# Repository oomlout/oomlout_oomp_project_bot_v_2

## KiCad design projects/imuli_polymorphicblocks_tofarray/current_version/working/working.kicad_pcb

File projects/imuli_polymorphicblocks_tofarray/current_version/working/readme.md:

# polymorphicblocks
 
## summary 
* id: imuli_polymorphicblocks_tofarray
* user: imuli
* name: polymorphicblocks
* board: tofarray
* repo: https://github.com/imuli/PolymorphicBlocks
* src_file_repo_kicad_pcb: examples/TofArray/TofArray.kicad_pcb
* src_file_repo_kicad_pcb_link: https://github.com/imuli/PolymorphicBlocks/tree/master/examples/TofArray/TofArray.kicad_pcb

* src_file_repo_sch: 
* src_file_repo_sch_link: https://github.com/imuli/PolymorphicBlocks/tree/master/
* full details link: https://github.com/oomlout/oomlout_oomp_project_bot_v_2/tree/main/projects/imuli_polymorphicblocks_tofarray/current_version/working

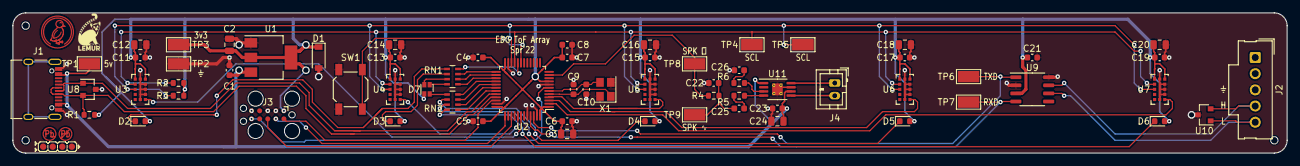
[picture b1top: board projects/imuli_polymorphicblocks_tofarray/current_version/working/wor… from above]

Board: 2 copper layers, 200.0 x 22.0 mm, 74 parts (0 on the bottom side), 47 nets.

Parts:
1: Indicator_LeadFree
2: Indicator_IdDots_4
C1, C4, C5, C6, C11, C13, C15, C17, C19, C21, C23: C14663; C_0603_1608Metric
C2, C3, C12, C14, C16, C18, C20, C24: C1779; C_0805_2012Metric
C7: C57112; C_0603_1608Metric
C8, C25, C26: C15849; C_0603_1608Metric
C9, C10: C1663; C_0603_1608Metric
C22: C1622; C_0603_1608Metric
D1: C499796; D_SOD-123
D2, D3, D4, D5, D6: C2286; LED_0603_1608Metric
D7: C264517; LED_LiteOn_LTST-C19HE1WT
H1, H2, H3: JlcToolingHole_1.152mm
J1: C165948; USB_C_Receptacle_XKB_U262-16XN-4BVC11
J2: Molex_SL_171971-0005_1x05_P2.54mm_Vertical
J3: Tag-Connect_TC2050-IDC-FP_2x05_P1.27mm_Vertical
J4: JST_PH_B2B-PH-K_1x02_P2.00mm_Vertical
R1: C22843; R_0603_1608Metric
R2, R3: C23162; R_0603_1608Metric
R4: C21190; R_0603_1608Metric
R5, R6: C22984; R_0603_1608Metric
RN1, RN2: C20197; R_Array_Concave_4x0603
SW1: C318884; SW_SPST_SKQG_WithoutStem
TP1, TP2, TP3, TP4, TP5, TP6, TP7, TP8, TP9: C238130; TestPoint_Keystone_5015_Micro-Minature
U1: C86781; SOT-223-3_TabPin2
U2: C8734; LQFP-48_7x7mm_P0.5mm
U3, U4, U5, U6, U7: C91199; ST_VL53L0X
U8: C87911; SOT-23
U9: C12084; SO-8_3.9x4.9mm_P1.27mm
U10: SOT-23
U11: C27396; MSOP-8-1EP_3x3mm_P0.65mm_EP1.68x1.88mm_ThermalVias
U12: Symbol_Duckling
U13: Symbol_LemurSmall
X1: C9002; Crystal_SMD_3225-4Pin_3.2x2.5mm

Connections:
can_chain_0.rxd: TP7.1, U2.45, U9.4
can_chain_0.txd: TP6.1, U2.46, U9.1
can_chain_1.canh: J2.4, U9.7, U10.2
can_chain_1.canl: J2.5, U9.6, U10.1
gnd: C1.2, C2.2, C3.2, C4.2, C5.2, C6.2, C7.2, C8.2, C9.2, C10.2, C11.2, C12.2, C13.2, C14.2, C15.2, C16.2, C17.2, C18.2, C19.2, C20.2, C21.2, C22.2, C23.2, C24.2, C26.2, D1.2, J1.A1, J1.A12, J1.B1, J1.B12, J2.3, J3.2, J3.3, J3.5, SW1.1, TP2.1, U1.1, U2.8, U2.23, U2.35, U2.44, U2.47, U3.2, U3.3, U3.4, U3.6, U3.12, U4.2, U4.3, U4.4, U4.6, U4.12, U5.2, U5.3, U5.4, U5.6, U5.12, U6.2, U6.3, U6.4, U6.6, U6.12, U7.2, U7.3, U7.4, U7.6, U7.12, U8.3, U9.2, U9.8, U10.3, U11.7, U11.9, X1.2, X1.4
i2c_chain_0.scl: R2.2, TP4.1, U2.21, U3.10, U4.10, U5.10, U6.10, U7.10
i2c_chain_0.sda: R3.2, TP5.1, U2.22, U3.9, U4.9, U5.9, U6.9, U7.9
leds_chain_0.0: RN1.8, U2.20
leds_chain_0.1: RN1.7, U2.25
leds_chain_0.2: RN2.7, U2.29
leds_chain_0.3: RN2.6, U2.30
leds_chain_0.4: RN2.5, U2.31
leds_chain_0.5: RN1.6, U2.26
leds_chain_0.6: RN1.5, U2.27
leds_chain_0.7: RN2.8, U2.28
mcu.crystal.crystal.a: C9.1, U2.5, X1.1
mcu.gpio.tof_xshut_1: U2.41, U4.5
mcu.gpio.tof_xshut_2: U2.4, U5.5
mcu.gpio.tof_xshut_3: U2.3, U6.5
mcu.ic.osc.xtal_out: C10.1, U2.6, X1.3
mcu.ic.swd.swclk: J3.9, U2.37
mcu.ic.swd.swo: J3.8, U2.39
mcu.swd.swd.reset: J3.6, U2.7
mcu.swd.swd.swdio: J3.10, U2.34
res1.a.0: D2.1, RN1.1
res1.a.1: D3.1, RN1.2
res1.a.2: D7.3, RN1.3
res1.a.3: D7.4, RN1.4
res2.a.0: D7.1, RN2.1
res2.a.1: D4.1, RN2.2
res2.a.2: D5.1, RN2.3
res2.a.3: D6.1, RN2.4
spk_chain_0: R4.1, TP8.1, U2.11
spk_chain_1: C22.1, C25.2, R4.2, TP9.1
spk_chain_2.a: J4.1, U11.8
spk_chain_2.b: J4.2, U11.5
spk_drv.(adapter)inn_res.b.src: R6.2, U11.3
spk_drv.(adapter)inp_res.b.dst: R5.2, U11.4
spk_drv.inn_cap.pos: C26.1, R6.1
spk_drv.inp_res.a: C25.1, R5.1
sw1_chain_0: SW1.2, U2.19
tof.xshut.0: U2.42, U3.5
tof.xshut.4: U2.2, U7.5
usb_chain_0.d_N: J1.A7, J1.B7, U2.32, U8.1
usb_chain_0.d_P: J1.A6, J1.B6, R1.2, U2.33, U8.2
v3v3: C2.1, C3.1, C4.1, C5.1, C6.1, C7.1, C8.1, C11.1, C12.1, C13.1, C14.1, C15.1, C16.1, C17.1, C18.1, C19.1, C20.1, C21.1, D1.1, D2.2, D3.2, D4.2, D5.2, D6.2, D7.2, J3.1, R1.1, R2.1, R3.1, TP3.1, U1.2, U2.1, U2.9, U2.24, U2.36, U2.48, U3.1, U3.11, U4.1, U4.11, U5.1, U5.11, U6.1, U6.11, U7.1, U7.11, U9.3
vusb: C1.1, C23.1, C24.1, J1.A4, J1.A9, J1.B4, J1.B9, TP1.1, U1.3, U11.1, U11.6

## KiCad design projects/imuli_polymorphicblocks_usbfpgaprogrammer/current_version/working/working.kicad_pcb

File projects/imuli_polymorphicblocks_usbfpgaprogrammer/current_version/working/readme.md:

# polymorphicblocks
 
## summary 
* id: imuli_polymorphicblocks_usbfpgaprogrammer
* user: imuli
* name: polymorphicblocks
* board: usbfpgaprogrammer
* repo: https://github.com/imuli/PolymorphicBlocks
* src_file_repo_kicad_pcb: examples/UsbFpgaProgrammer/UsbFpgaProgrammer.kicad_pcb
* src_file_repo_kicad_pcb_link: https://github.com/imuli/PolymorphicBlocks/tree/master/examples/UsbFpgaProgrammer/UsbFpgaProgrammer.kicad_pcb

* src_file_repo_sch: 
* src_file_repo_sch_link: https://github.com/imuli/PolymorphicBlocks/tree/master/
* full details link: https://github.com/oomlout/oomlout_oomp_project_bot_v_2/tree/main/projects/imuli_polymorphicblocks_usbfpgaprogrammer/current_version/working

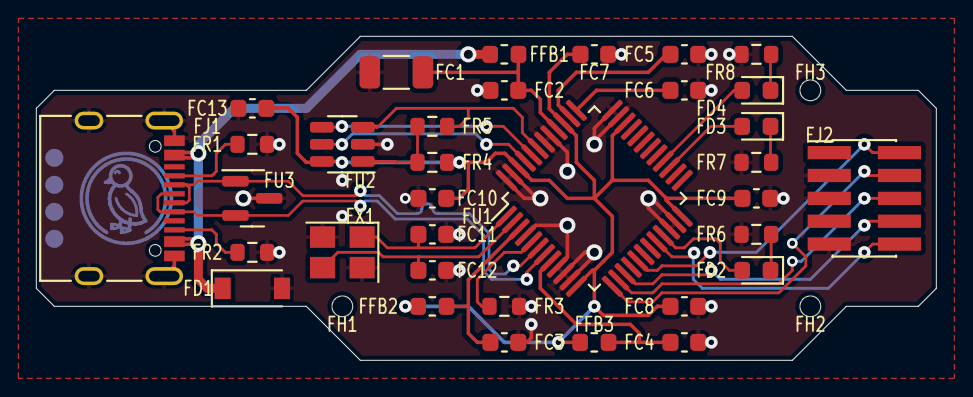
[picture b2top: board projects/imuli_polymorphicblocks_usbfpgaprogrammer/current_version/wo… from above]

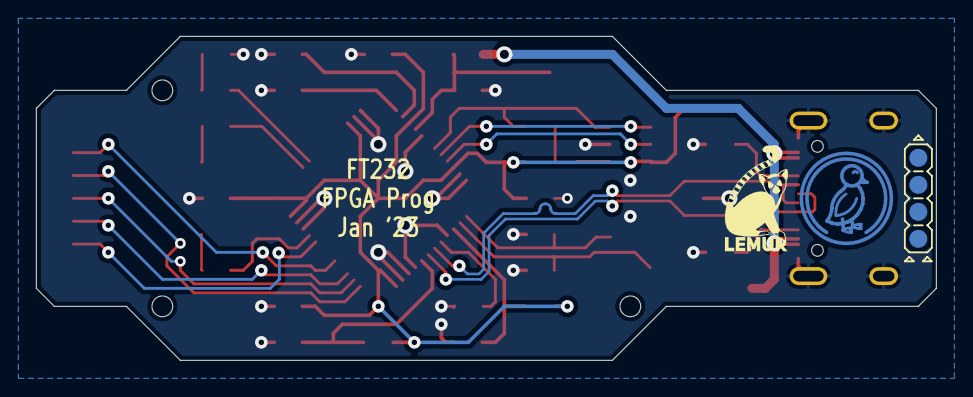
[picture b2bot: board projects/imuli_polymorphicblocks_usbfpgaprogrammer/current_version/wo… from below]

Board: 2 copper layers, 50.0 x 18.0 mm, 40 parts (3 on the bottom side), 30 nets.

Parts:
FC1: C_1206_3216Metric
FC2, FC3, FC4, FC5, FC6, FC7, FC8, FC9, FC10, FC11, FC12, FC13: C_0603_1608Metric
FD1: MMSZ5232A_R1_00001 (PANJIT International) - 5?A@3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; D_SOD-123
FD2: C2290 (Hubei KENTO Elec) - White 0603 Light Emitt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; LED_0603_1608Metric
FD3, FD4: LED_0603_1608Metric
FFB1, FFB2, FFB3: L_0603_1608Metric
FH1, FH2, FH3: JlcToolingHole_1.152mm
FJ1: COM-15111 (Sparkfun); USB_C_Receptacle_XKB_U262-16XN-4BVC11
FJ2: PinHeader1.27 Shrouded 2x5 (Generic); PinHeader_2x05_P1.27mm_Vertical_SMD
FR1, FR2, FR3, FR4, FR5, FR6, FR7, FR8: R_0603_1608Metric
FU1: FT232HL (FTDI, Future Technology Devices Internat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; LQFP-48_7x7mm_P0.5mm
FU2: 93LC56B (Microchip Technology); SOT-23-6
FU3: PGB102ST23 (Littelfuse); SOT-23
FU4: Duck; Symbol_Duckling
FU5: Lemur; Symbol_LemurSmall
FU6: IdDots4; Indicator_IdDots_4
FX1: Crystal_SMD_3225-4Pin_3.2x2.5mm

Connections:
ft232.acbus0: FD2.2, FU1.21
ft232.acbus3: FD3.2, FU1.27
ft232.acbus4: FD4.2, FU1.28
ft232.adbus4: FJ2.2, FU1.17
ft232.adbus7: FJ2.10, FU1.20
ft232.crystal.crystal.a: FC11.1, FU1.1, FX1.1
ft232.crystal.crystal.b: FC12.1, FU1.2, FX1.3
ft232.eeprom.cs: FU1.45, FU2.5
ft232.eeprom_spi.eeclk: FU1.44, FU2.4
ft232.eeprom_spi.eedata: FR5.2, FU1.43, FU2.3
ft232.eeprom_spi.spi.miso: FR4.2, FR5.1, FU2.1
ft232.ic.vcca: FC6.1, FU1.37
ft232.ic.vcccore: FC5.1, FU1.38
ft232.ic.vccd: FC7.1, FC8.1, FC9.1, FC10.1, FC13.1, FFB2.1, FFB3.1, FR4.1, FU1.12, FU1.24, FU1.34, FU1.39, FU1.46, FU2.6
ft232.ic.vphy: FC3.1, FFB2.2, FU1.3
ft232.ic.vpll: FC4.1, FFB3.2, FU1.8
ft232.ic.vregin: FC1.1, FC2.1, FFB1.2, FU1.40
ft232.mpsse.miso: FJ2.8, FU1.15
ft232.mpsse.mosi: FJ2.6, FU1.14
ft232.mpsse.sck: FJ2.4, FU1.13
ft232.ref_res.a: FR3.1, FU1.5
gnd: FC1.2, FC2.2, FC3.2, FC4.2, FC5.2, FC6.2, FC7.2, FC8.2, FC9.2, FC10.2, FC11.2, FC12.2, FC13.2, FD1.2, FJ1.A1, FJ1.A12, FJ1.B1, FJ1.B12, FJ1.S1, FJ2.3, FJ2.5, FJ2.9, FR1.1, FR2.1, FR3.2, FR6.2, FR7.2, FR8.2, FU1.4, FU1.9, FU1.10, FU1.11, FU1.22, FU1.23, FU1.35, FU1.36, FU1.41, FU1.42, FU1.47, FU1.48, FU2.2, FU3.3, FX1.2, FX1.4
led0.res.a: FD2.1, FR6.1
led1.res.a: FD3.1, FR7.1
led2.res.a: FD4.1, FR8.1
usb.conn.A5: FJ1.A5, FR1.2
usb.conn.B5: FJ1.B5, FR2.2
usb_chain_0.d_N: FJ1.A7, FJ1.B7, FU1.6, FU3.1
usb_chain_0.d_P: FJ1.A6, FJ1.B6, FU1.7, FU3.2
vusb: FD1.1, FFB1.1, FJ1.A4, FJ1.A9, FJ1.B4, FJ1.B9

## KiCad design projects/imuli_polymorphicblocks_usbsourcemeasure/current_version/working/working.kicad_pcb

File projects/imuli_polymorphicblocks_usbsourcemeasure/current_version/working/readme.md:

# polymorphicblocks
 
## summary 
* id: imuli_polymorphicblocks_usbsourcemeasure
* user: imuli
* name: polymorphicblocks
* board: usbsourcemeasure
* repo: https://github.com/imuli/PolymorphicBlocks
* src_file_repo_kicad_pcb: examples/UsbSourceMeasure/UsbSourceMeasure.kicad_pcb
* src_file_repo_kicad_pcb_link: https://github.com/imuli/PolymorphicBlocks/tree/master/examples/UsbSourceMeasure/UsbSourceMeasure.kicad_pcb

* src_file_repo_sch: 
* src_file_repo_sch_link: https://github.com/imuli/PolymorphicBlocks/tree/master/
* full details link: https://github.com/oomlout/oomlout_oomp_project_bot_v_2/tree/main/projects/imuli_polymorphicblocks_usbsourcemeasure/current_version/working

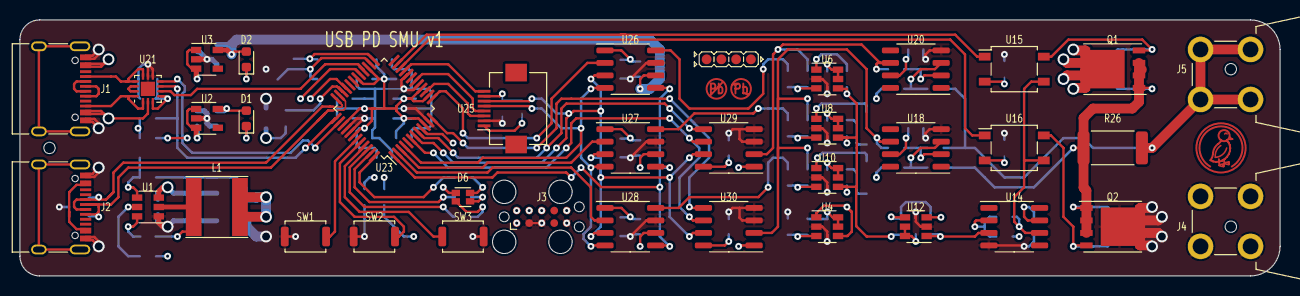
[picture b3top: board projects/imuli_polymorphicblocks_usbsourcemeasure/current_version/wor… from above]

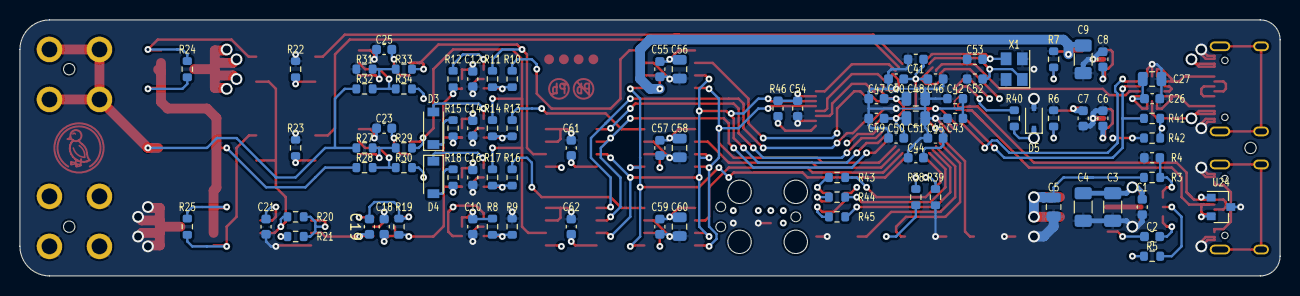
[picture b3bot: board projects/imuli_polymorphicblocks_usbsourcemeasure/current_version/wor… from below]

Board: 4 copper layers, 128.0 x 26.0 mm, 130 parts (88 on the bottom side), 82 nets.

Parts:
1: LeadFree; Indicator_LeadFree
2: IdDots4; Indicator_IdDots_4
3, 4, 5: JlcToolingHole_1.152mm
C1, C2, C10, C12, C14, C16, C18, C21, C23, C25, C26, C40, C42, C44, C46, C47, C49, C50, C55, C57, C59: CC0603KRX7R9BB104 (YAGEO) - X7R 100nF ±10% 50V 06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; C_0603_1608Metric
C3, C4: CL31A106KBHNNNE (Samsung Electro-Mechanics) - X5R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; C_1206_3216Metric
C5, C27, C48, C51, C56, C58, C60: CL21A106KAYNNNE (Samsung Electro-Mechanics) - X5R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; C_0805_2012Metric
C6, C7, C8, C54, C61, C62: CL10A105KB8NNNC (Samsung Electro-Mechanics) - X5R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; C_0603_1608Metric
C9: CL31B225KBHNNNE (Samsung Electro-Mechanics) - X7R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; C_1206_3216Metric
C19: 1nF; C_0603_1608Metric
C41, C43, C45: 0603B103K500NT (FH(Guangdong Fenghua Advanced Tec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; C_0603_1608Metric
C52, C53: CL10C100JB8NNNC (Samsung Electro-Mechanics) - C0G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; C_0603_1608Metric
D1, D2: LED; LED_0603_1608Metric
D3, D4: DSS14UTR (SMC Diode Solutions) - Vr=40V, I=1A; D_SOD-123
D5: DDZ3V6ASF-7 (Diodes Incorporated) - Vz=3.57V, I=9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; D_SOD-323
D6: EAST1616RGBB2 (Everlight Electronics Co Ltd); LED_LiteOn_LTST-C19HE1WT
J1, J2: COM-15111 (Sparkfun); USB_C_Receptacle_XKB_U262-16XN-4BVC11
J3: SWD; Tag-Connect_TC2050-IDC-FP_2x05_P1.27mm_Vertical
J4, J5: CT3151-* (CalTest); CalTest_CT3151
L1: NR6028T470M (Taiyo Yuden) - 47µH, 920mA; L_Taiyo-Yuden_NR-60xx
Q1: SIR172ADP-T1-GE3 (Vishay Siliconix) - Vds=30 V, I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; PowerPAK_SO-8_Single
Q2: SQJ433EP-T1_GE3 (Vishay Siliconix) - Vds=30 V, Id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; PowerPAK_SO-8_Single
R3: 0603WAF1102T5E (UNI-ROYAL(Uniroyal Elec)) - 11kΩ 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; R_0603_1608Metric
R4: 0603WAF1501T5E (UNI-ROYAL(Uniroyal Elec)) - 1.5kΩ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; R_0603_1608Metric
R5: 0603WAF5103T5E (UNI-ROYAL(Uniroyal Elec)) - ±1% 5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; R_0603_1608Metric
R6, R7, R43, R44, R45: 0603WAF6800T5E (UNI-ROYAL(Uniroyal Elec)) - 680Ω 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; R_0603_1608Metric
R8, R9: 0603WAF1003T5E (UNI-ROYAL(Uniroyal Elec)) - ±1% 1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; R_0603_1608Metric
R10, R11, R13, R14, R16, R17, R27, R28, R29, R30, R33, R34, R40: 0603WAF1002T5E (UNI-ROYAL(Uniroyal Elec)) - ±1% ±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; R_0603_1608Metric
R12, R19, R24, R25, R41, R42: 0603WAF4701T5E (UNI-ROYAL(Uniroyal Elec)) - ±1% 4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; R_0603_1608Metric
R15, R18: 0603WAF100KT5E (UNI-ROYAL(Uniroyal Elec)) - ±1% ±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; R_0603_1608Metric
R20: 0603WAF3902T5E (UNI-ROYAL(Uniroyal Elec)) - ±1% 3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; R_0603_1608Metric
R21: 0603WAF2001T5E (UNI-ROYAL(Uniroyal Elec)) - ±1% 2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; R_0603_1608Metric
R22, R23: 0603WAF1600T5E (UNI-ROYAL(Uniroyal Elec)) - ±1% ±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; R_0603_1608Metric
R26: 100m, 1%, 1.0 W; R_2512_6332Metric
R31, R32: 0603WAF2203T5E (UNI-ROYAL(Uniroyal Elec)) - ±1% ±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; R_0603_1608Metric
R38, R39: 0603WAF1502T5E (UNI-ROYAL(Uniroyal Elec)) - ±1% 1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; R_0603_1608Metric
R46: 0603WAF1000T5E (UNI-ROYAL(Uniroyal Elec)) - ±1% ±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; R_0603_1608Metric
SW1, SW2, SW3: 3.9x2.9mm Switch; SW_Push_SPST_NO_Alps_SKRK
U1: TPS54202H (Texas Instruments); SOT-23-6
U2: XC6209F332MR-G (Torex Semiconductor Ltd); SOT-23-5
U3: AP2210K-3.0 (Torex Semiconductor Ltd); SOT-23-5
U4, U6, U8, U10, U12: TLV9061SQDBVRQ1 (Texas Instruments); SOT-23-6
U14, U18, U20: OPA197IDR (Texas Instruments); SO-8_3.9x4.9mm_P1.27mm
U15, U16: G3VM-61GR2 (Omron Electronics); SO-4_4.4x4.3mm_P2.54mm
U21: FUSB302B11MPX (ON Semiconductor); WQFN-14-1EP_2.5x2.5mm_P0.5mm_EP1.45x1.45mm
U23: LPC1549JBD48 (NXP); LQFP-48_7x7mm_P0.5mm
U24: TPD2E009 (Texas Instruments); SOT-23
U25: QT096T_IF09, FH12-8S-0.5SH(55); Hirose_FH12-8S-0.5SH_1x08-1MP_P0.50mm_Horizontal
U26, U27, U28: MCP4921-E/SN (Microchip Technology); SO-8_3.9x4.9mm_P1.27mm
U29, U30: MCP3201T-BI/SN (Microchip Technology); SO-8_3.9x4.9mm_P1.27mm
U31: Duck; Symbol_Duckling
X1: ABM8G-106-12.000MHZ-T (Abracon LLC) - 12MHz, 10pF; Oscillator_SMD_Abracon_ASE-4Pin_3.2x2.5mm

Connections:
adc_i_cs_net: U23.12, U30.5
adc_v.vin: R11.1, R33.1, U20.6, U29.2
adc_v_cs_net: U23.8, U29.5
control.amp.input: C19.1, U12.1, U14.3
control.amp.r2.a: R20.2, R21.1, U14.2
control.control_current_source: R13.1, U27.8
control.control_voltage: R10.1, U26.8
control.driver.(adapter)high_res.b.src: Q1.4, R24.2, U15.4
control.driver.control: R20.1, U14.6, U15.3, U16.3
control.driver.high_gate.ic.ledk: R22.1, U15.2
control.driver.low_gate.apull: Q2.4, R25.2, U16.4
control.driver.low_gate.ic.ledk: R23.1, U16.2
control.driver.out: Q1.1, Q1.2, Q1.3, Q2.1, Q2.2, Q2.3, R24.1, R25.1, R26.1, R28.1
control.err_sink.(adapter)diode.anode.src: D4.2, R18.1
control.err_sink.(adapter)diode.cathode.dst: D4.1, U10.1
control.err_sink.(adapter)rbot.b.dst: R16.2, R17.2, U10.3
control.err_source.(adapter)rout.a.dst: D3.1, R15.1
control.err_source.diode.anode: D3.2, U8.1
control.err_source.rtop.b: R13.2, R14.2, U8.3
control.err_volt.(adapter)rout.a.dst: R12.1, U6.1
control.err_volt.amp.inp: R10.2, R11.2, U6.3
control.imeas.(adapter)r2.b.dst: R28.2, R30.2, U18.3
control.imeas.(adapter)rf.b.dst: R27.2, R29.2, U18.2
control.int.(adapter)r.b.dst: C19.2, R19.2, U12.4
control.int_link: R12.2, R15.2, R18.2, R19.1, U6.4, U8.4, U10.4
control.measured_current: R14.1, R17.1, R29.1, U18.6, U30.2
control.vmeas.r2.b: R32.2, R34.2, U20.3
control.vmeas.rf.b: R31.2, R33.2, U20.2
crystal.crystal.a: C52.1, U23.26, X1.1
dac_in.out: R16.1, U28.8
dac_in_cs_net: U23.2, U28.2
dac_ip_cs_net: U23.3, U27.2
dac_ldac_net: U23.1, U26.5, U27.5, U28.5
dac_v_cs_net: U23.13, U26.2
data_usb.B4: J2.A4, J2.A9, J2.B4, J2.B9
gnd: C1.2, C3.2, C4.2, C5.2, C6.2, C7.2, C8.2, C9.2, C10.2, C12.2, C14.2, C16.2, C18.2, C21.2, C23.2, C25.2, C26.2, C27.2, C40.2, C41.2, C42.2, C43.2, C44.2, C45.2, C46.2, C47.2, C48.2, C49.2, C50.2, C51.2, C52.2, C53.2, C54.2, C55.2, C56.2, C57.2, C58.2, C59.2, C60.2, C61.2, C62.2, D5.2, J1.A1, J1.A12, J1.B1, J1.B12, J2.A1, J2.A12, J2.B1, J2.B12, J3.2, J3.3, J3.5, J4.1, Q2.5, R4.2, R6.2, R7.2, R9.2, R22.2, R23.2, R31.1, R39.1, SW1.1, SW2.1, SW3.1, U1.1, U2.2, U3.2, U4.2, U6.2, U8.2, U10.2, U12.2, U14.4, U18.4, U20.4, U21.8, U21.9, U21.15, U23.11, U23.17, U23.20, U23.40, U23.41, U24.3, U25.2, U26.7, U27.7, U28.7, U29.3, U29.4, U30.3, U30.4, X1.2, X1.4
high_en_net: U15.1, U23.23
i2c_pull.i2c.sda: R42.2, U21.7, U23.38
lcd.device.leda: R46.2, U25.1
lcd_cs_net: U23.21, U25.8
lcd_reset_net: U23.15, U25.3
lcd_rs_net: U23.18, U25.4
led_3v3.res.a: D1.1, R6.1
led_analog.package.k: D2.1, R7.1
low_en_net: U16.1, U23.22
mcu.i2c_0.scl: R41.2, U21.6, U23.37
mcu.swd.reset: J3.6, R40.2, U23.34
mcu.swd.swdio: J3.10, R38.2, U23.33
mcu.swd.swo: J3.8, U23.9
mcu.usb_0.dp: J2.A6, J2.B6, U23.35, U24.2
mcu.xtal.xtal_out: C53.1, U23.25, X1.3
outp.port: J5.1, R26.2, R27.1, R32.1
pd.cc.cc2: J1.B5, U21.1, U21.14
pd.ic.vconn: U21.12, U21.13
pd_int_net: U21.5, U23.28
pwr_usb.cc.cc1: J1.A5, U21.10, U21.11
pwr_usb.usb.dm: J1.A7, J1.B7
pwr_usb.usb.dp: J1.A6, J1.B6
ref_div.center: R8.2, R9.1, U4.3
reg_5v.(adapter)boot_cap.pos.dst: C2.1, U1.6
reg_5v._pwr_out_net: C5.1, C6.1, C8.1, L1.2, R3.1, U2.1, U2.3, U3.1, U3.3
reg_5v._switch_net: C2.2, L1.1, U1.2
reg_5v.en_res.b: R5.2, U1.5
reg_5v.ic.fb: R3.2, R4.1, U1.4
rgb.green_res.a: D6.4, R44.1
rgb.package.k_blue: D6.1, R45.1
rgb.package.k_red: D6.3, R43.1
rgb_b_net: R45.2, U23.46
rgb_g_net: R44.2, U23.47
rgb_r_net: R43.2, U23.48
spi_net.miso: U23.6, U29.6, U30.6
spi_net.mosi: U23.4, U25.5, U26.4, U27.4, U28.4
spi_net.sck: U23.7, U25.6, U26.3, U27.3, U28.3, U29.7, U30.7
sw1_chain_0: SW1.2, U23.43
sw2_chain_0: SW2.2, U23.44
sw3_chain_0: SW3.2, U23.45
swd.swd.swclk: J3.9, R39.2, U23.29
usb_esd.usb.dm: J2.A7, J2.B7, U23.36, U24.1
v3v3: C7.1, C12.1, C14.1, C16.1, C18.1, C26.1, C27.1, C40.1, C41.1, C42.1, C43.1, C44.1, C45.1, C46.1, C47.1, C48.1, C49.1, C50.1, C51.1, C54.1, C55.1, C56.1, C57.1, C58.1, C59.1, C60.1, C61.1, C62.1, D1.2, D5.1, D6.2, J3.1, R38.1, R40.1, R41.1, R42.1, R46.1, U2.5, U6.5, U6.6, U8.5, U8.6, U10.5, U10.6, U12.5, U12.6, U21.3, U21.4, U23.10, U23.14, U23.16, U23.27, U23.30, U23.39, U23.42, U25.7, U26.1, U27.1, U28.1, U29.8, U30.8
vanalog: C9.1, C10.1, D2.2, R8.1, U3.5, U4.5, U4.6, U26.6, U27.6, U28.6, U29.1, U30.1
vcenter: R21.2, R30.1, R34.1, U4.1, U4.4, U12.3
vusb: C1.1, C3.1, C4.1, C21.1, C23.1, C25.1, J1.A4, J1.A9, J1.B4, J1.B9, Q1.5, R5.1, U1.3, U14.7, U18.7, U20.7, U21.2

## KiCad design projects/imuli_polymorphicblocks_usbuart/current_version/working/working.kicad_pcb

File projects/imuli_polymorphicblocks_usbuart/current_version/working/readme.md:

# polymorphicblocks
 
## summary 
* id: imuli_polymorphicblocks_usbuart
* user: imuli
* name: polymorphicblocks
* board: usbuart
* repo: https://github.com/imuli/PolymorphicBlocks
* src_file_repo_kicad_pcb: examples/UsbUart/UsbUart.kicad_pcb
* src_file_repo_kicad_pcb_link: https://github.com/imuli/PolymorphicBlocks/tree/master/examples/UsbUart/UsbUart.kicad_pcb

* src_file_repo_sch: 
* src_file_repo_sch_link: https://github.com/imuli/PolymorphicBlocks/tree/master/
* full details link: https://github.com/oomlout/oomlout_oomp_project_bot_v_2/tree/main/projects/imuli_polymorphicblocks_usbuart/current_version/working

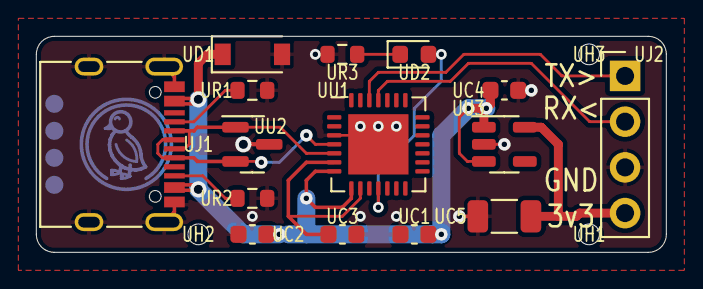
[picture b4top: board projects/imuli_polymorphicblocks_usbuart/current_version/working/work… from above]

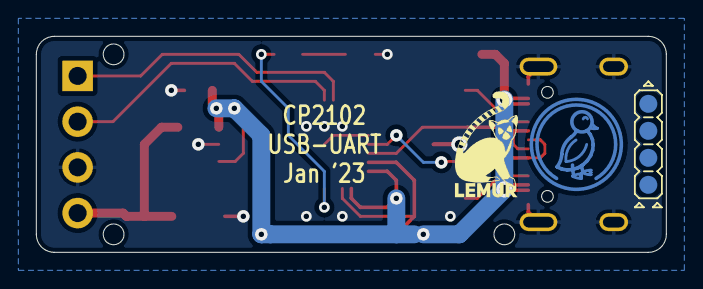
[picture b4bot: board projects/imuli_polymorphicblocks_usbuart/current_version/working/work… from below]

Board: 2 copper layers, 35.0 x 12.0 mm, 21 parts (3 on the bottom side), 12 nets.

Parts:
UC1, UC2, UC3, UC4: C_0603_1608Metric
UC5: C_1206_3216Metric
UD1: MMSZ5232A_R1_00001 (PANJIT International) - 5?A@3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; D_SOD-123
UD2: C2290 (Hubei KENTO Elec) - White 0603 Light Emitt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; LED_0603_1608Metric
UH1, UH2, UH3: JlcToolingHole_1.152mm
UJ1: COM-15111 (Sparkfun); USB_C_Receptacle_XKB_U262-16XN-4BVC11
UJ2: PinHeader2.54 1x4 (Generic); PinHeader_1x04_P2.54mm_Vertical
UR1, UR2, UR3: R_0603_1608Metric
UU1: CP2102 (Silicon Labs); QFN-28-1EP_5x5mm_P0.5mm_EP3.35x3.35mm
UU2: PGB102ST23 (Littelfuse); SOT-23
UU3: AP2204K-3.3 (Diodes Incorporated); SOT-23-5
UU4: Duck; Symbol_Duckling
UU5: Lemur; Symbol_LemurSmall
UU6: IdDots4; Indicator_IdDots_4

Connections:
gnd: UC1.2, UC2.2, UC3.2, UC4.2, UC5.2, UD1.2, UJ1.A1, UJ1.A12, UJ1.B1, UJ1.B12, UJ1.S1, UJ2.3, UR1.1, UR2.1, UR3.2, UU1.3, UU1.29, UU2.3, UU3.2
led.res.a: UD2.1, UR3.1
usb_chain_0.d_N: UJ1.A7, UJ1.B7, UU1.5, UU2.1
usb_chain_0.d_P: UJ1.A6, UJ1.B6, UU1.4, UU2.2
usb_uart.conn.A5: UJ1.A5, UR1.2
usb_uart.conn.B5: UJ1.B5, UR2.2
usbconv.ic.vdd: UC3.1, UU1.6, UU1.9
usbconv.nsuspend: UD2.2, UU1.11
usbconv.uart.rx: UJ2.2, UU1.25
usbconv.uart.tx: UJ2.1, UU1.26
v3v3: UC5.1, UJ2.4, UU3.5
vusb: UC1.1, UC2.1, UC4.1, UD1.1, UJ1.A4, UJ1.A9, UJ1.B4, UJ1.B9, UU1.7, UU1.8, UU3.1, UU3.3

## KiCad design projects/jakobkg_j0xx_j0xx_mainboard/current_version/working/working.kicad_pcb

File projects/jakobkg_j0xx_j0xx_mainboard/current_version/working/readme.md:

# j0xx
 
## summary 
* id: jakobkg_j0xx_j0xx_mainboard
* user: jakobkg
* name: j0xx
* board: j0xx_mainboard
* repo: https://github.com/jakobkg/j0xx
* src_file_repo_kicad_pcb: pcb/mainboard/j0xx-mainboard.kicad_pcb
* src_file_repo_kicad_pcb_link: https://github.com/jakobkg/j0xx/tree/main/pcb/mainboard/j0xx-mainboard.kicad_pcb
* src_file_repo_kicad_sch: pcb/mainboard/j0xx-mainboard.kicad_sch
* src_file_repo_kicad_sch_link: https://github.com/jakobkg/j0xx/tree/main/pcb/mainboard/j0xx-mainboard.kicad_sch

* src_file_repo_sch: 
* src_file_repo_sch_link: https://github.com/jakobkg/j0xx/tree/main/
* full details link: https://github.com/oomlout/oomlout_oomp_project_bot_v_2/tree/main/projects/jakobkg_j0xx_j0xx_mainboard/current_version/working

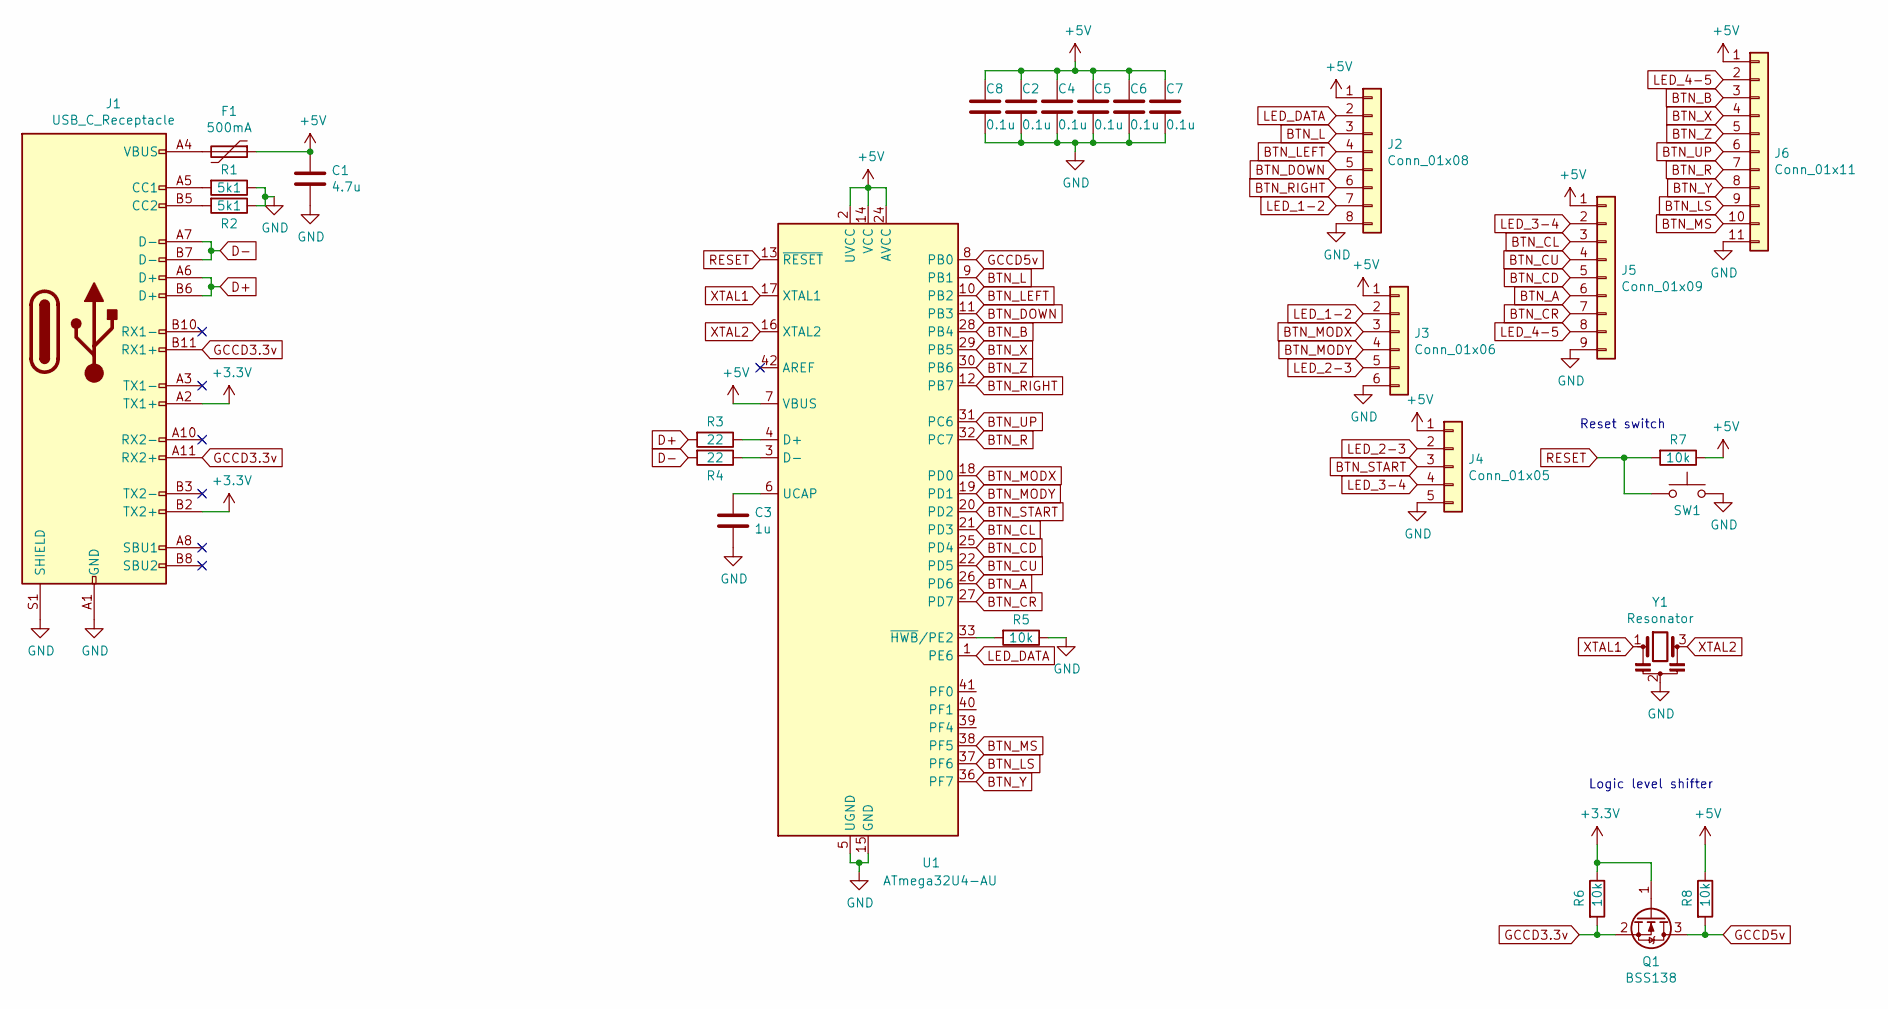
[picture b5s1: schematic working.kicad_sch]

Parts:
C1: 4.7u; C_0805_2012Metric; LCSC C1779
C2, C4, C5, C6, C7, C8: 0.1u; C_0805_2012Metric; LCSC C28233
C3: 1u; C_0805_2012Metric; LCSC C28323
F1: 500mA; Fuse_1206_3216Metric; LCSC C261952
J1: USB_C_Receptacle; USB_C_LCSC_C456013; LCSC C456013
J2: Conn_01x08; PinHeader_1x08_P2.54mm_Vertical
J3: Conn_01x06; PinHeader_1x06_P2.54mm_Vertical
J4: Conn_01x05; PinHeader_1x05_P2.54mm_Vertical
J5: Conn_01x09; PinHeader_1x09_P2.54mm_Vertical
J6: Conn_01x11; PinHeader_1x11_P2.54mm_Vertical
Q1: BSS138; SOT-23; LCSC C427380
R1, R2: 5k1; R_0805_2012Metric; LCSC C27834
R3, R4: 22; R_0805_2012Metric; LCSC C17561
R5, R6, R7, R8: 10k; R_0805_2012Metric; LCSC C17414
SW1: reset; TestPoint_2Pads_Pitch2.54mm_Drill0.8mm
U1: ATmega32U4-AU; TQFP-44_10x10mm_P0.8mm; LCSC C112161
Y1: Resonator; Resonator_SMD_Murata_CSTxExxV-3Pin_3.0x1.1mm; LCSC C341521

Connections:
+3V3: J1.A2 (TX1+), J1.B2 (TX2+), Q1.1 (G), R6.1
+5V: C1.1, C2.1, C4.1, C5.1, C6.1, C7.1, C8.1, F1.1, J2.1, J3.1, J4.1, J5.1, J6.1, R7.1, R8.1, U1.2 (UVCC), U1.7 (VBUS), U1.14 (VCC), U1.24 (AVCC), U1.34 (VCC), U1.44 (AVCC)
BTN_A: J5.6, U1.26 (PD6)
BTN_B: J6.3, U1.28 (PB4)
BTN_CD: J5.5, U1.25 (PD4)
BTN_CL: J5.3, U1.21 (PD3)
BTN_CR: J5.7, U1.27 (PD7)
BTN_CU: J5.4, U1.22 (PD5)
BTN_DOWN: J2.5, U1.11 (PB3)
BTN_L: J2.3, U1.9 (PB1)
BTN_LEFT: J2.4, U1.10 (PB2)
BTN_LS: J6.9, U1.37 (PF6)
BTN_MODX: J3.3, U1.18 (PD0)
BTN_MODY: J3.4, U1.19 (PD1)
BTN_MS: J6.10, U1.38 (PF5)
BTN_R: J6.7, U1.32 (PC7)
BTN_RIGHT: J2.6, U1.12 (PB7)
BTN_START: J4.3, U1.20 (PD2)
BTN_UP: J6.6, U1.31 (PC6)
BTN_X: J6.4, U1.29 (PB5)
BTN_Y: J6.8, U1.36 (PF7)
BTN_Z: J6.5, U1.30 (PB6)
D+: J1.A6 (D+), J1.B6 (D+), R3.2
D-: J1.A7 (D-), J1.B7 (D-), R4.2
GCCD3.3v: J1.A11 (RX2+), J1.B11 (RX1+), Q1.2 (S), R6.2
GCCD5v: Q1.3 (D), R8.2, U1.8 (PB0)
GND: C1.2, C2.2, C3.2, C4.2, C5.2, C6.2, C7.2, C8.2, J1.A1 (GND), J1.A12 (GND), J1.B1 (GND), J1.B12 (GND), J1.S1 (SHIELD), J2.8, J3.6, J4.5, J5.9, J6.11, R1.1, R2.1, R5.1, SW1.2, U1.5 (UGND), U1.15 (GND), U1.23 (GND), U1.35 (GND), U1.43 (GND), Y1.2
LED_1-2: J2.7, J3.2
LED_2-3: J3.5, J4.2
LED_3-4: J4.4, J5.2
LED_4-5: J5.8, J6.2
LED_DATA: J2.2, U1.1 (PE6)
unnamed: C3.1, U1.6 (UCAP)
unnamed: F1.2, J1.A4 (VBUS), J1.A9 (VBUS), J1.B4 (VBUS), J1.B9 (VBUS)
unnamed: J1.A5 (CC1), R1.2
unnamed: J1.B5 (CC2), R2.2
unnamed: R3.1, U1.4 (D+)
unnamed: R4.1, U1.3 (D-)
unnamed: R5.2, U1.33 (~HWB/PE2)
RESET: R7.2, SW1.1, U1.13 (~RESET)
XTAL1: U1.17 (XTAL1), Y1.1
XTAL2: U1.16 (XTAL2), Y1.3

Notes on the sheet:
Logic level shifter
Reset switch

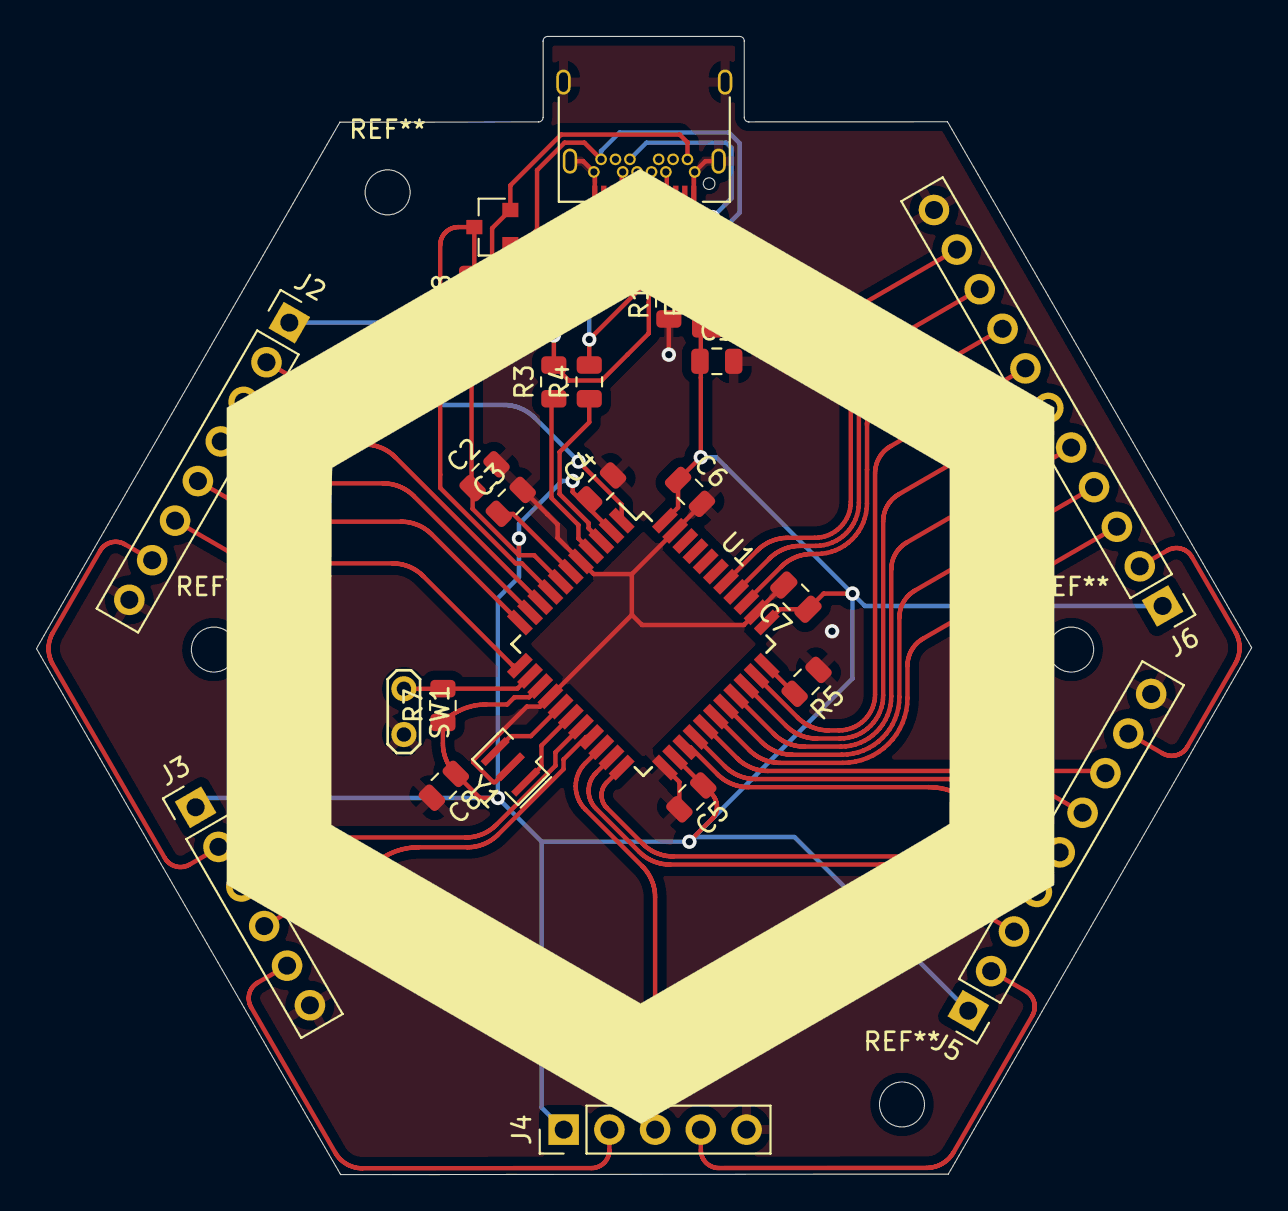
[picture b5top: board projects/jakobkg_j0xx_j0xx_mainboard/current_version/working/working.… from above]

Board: 2 copper layers, 67.5 x 63.2 mm, 27 parts (0 on the bottom side), 42 nets.

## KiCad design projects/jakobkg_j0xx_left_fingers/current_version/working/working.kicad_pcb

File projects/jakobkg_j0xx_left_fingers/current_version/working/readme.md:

# j0xx
 
## summary 
* id: jakobkg_j0xx_left_fingers
* user: jakobkg
* name: j0xx
* board: left_fingers
* repo: https://github.com/jakobkg/j0xx
* src_file_repo_kicad_pcb: pcb/left_fingers/left_fingers.kicad_pcb
* src_file_repo_kicad_pcb_link: https://github.com/jakobkg/j0xx/tree/main/pcb/left_fingers/left_fingers.kicad_pcb
* src_file_repo_kicad_sch: pcb/left_fingers/left_fingers.kicad_sch
* src_file_repo_kicad_sch_link: https://github.com/jakobkg/j0xx/tree/main/pcb/left_fingers/left_fingers.kicad_sch

* src_file_repo_sch: 
* src_file_repo_sch_link: https://github.com/jakobkg/j0xx/tree/main/
* full details link: https://github.com/oomlout/oomlout_oomp_project_bot_v_2/tree/main/projects/jakobkg_j0xx_left_fingers/current_version/working

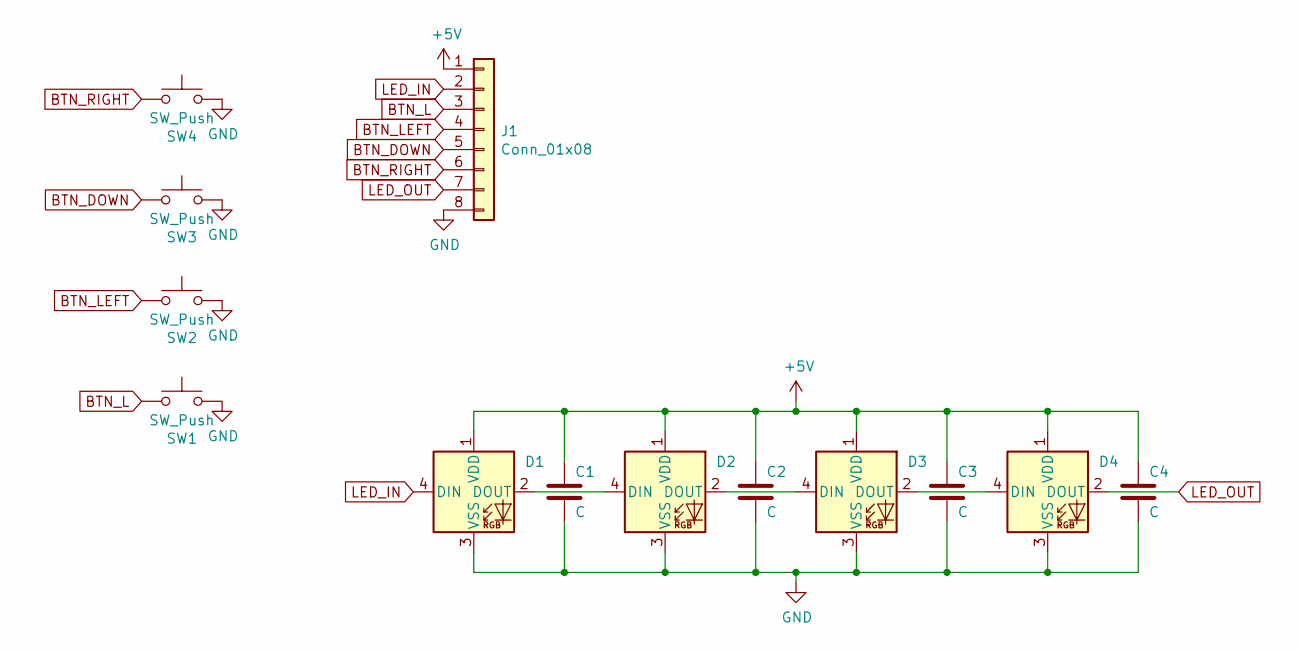
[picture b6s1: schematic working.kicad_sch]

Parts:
C1, C2, C3, C4: C; C_0805_2012Metric
D1, D2, D3, D4: WS2812B; LED_WS2812B_PLCC4_5.0x5.0mm_P3.2mm
J1: Conn_01x08; PinHeader_1x08_P2.54mm_Vertical
SW1, SW2, SW3, SW4: SW_Push; MX+Choc_socket

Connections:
+5V: C1.1, C2.1, C3.1, C4.1, D1.1 (VDD), D2.1 (VDD), D3.1 (VDD), D4.1 (VDD), J1.1
BTN_DOWN: J1.5, SW3.1
BTN_L: J1.3, SW1.1
BTN_LEFT: J1.4, SW2.1
BTN_RIGHT: J1.6, SW4.1
GND: C1.2, C2.2, C3.2, C4.2, D1.3 (VSS), D2.3 (VSS), D3.3 (VSS), D4.3 (VSS), J1.8, SW1.2, SW2.2, SW3.2, SW4.2
LED_IN: D1.4 (DIN), J1.2
LED_OUT: D4.2 (DOUT), J1.7
unnamed: D1.2 (DOUT), D2.4 (DIN)
unnamed: D2.2 (DOUT), D3.4 (DIN)
unnamed: D3.2 (DOUT), D4.4 (DIN)

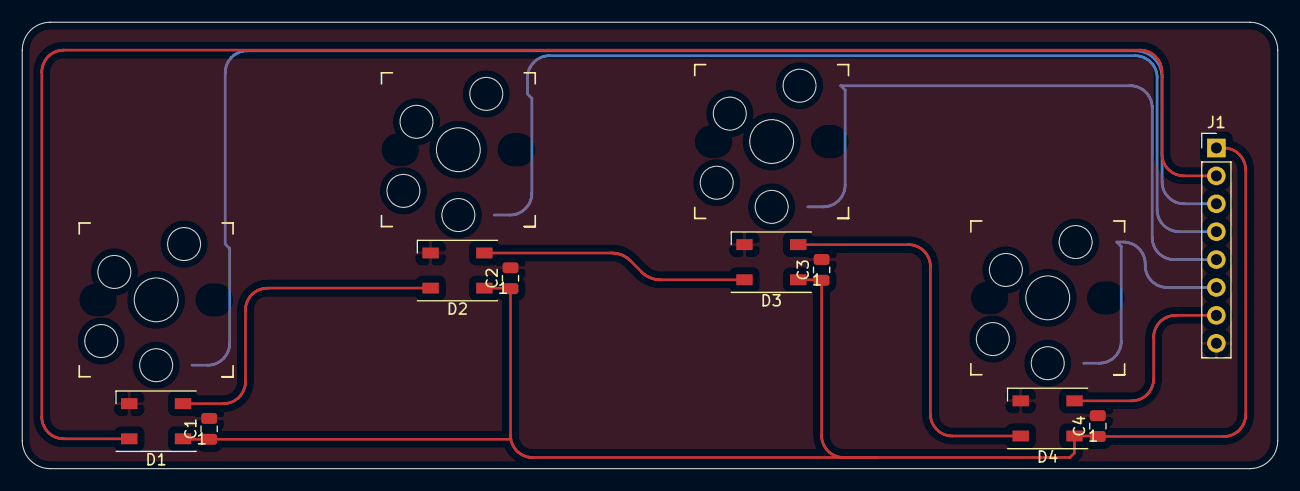
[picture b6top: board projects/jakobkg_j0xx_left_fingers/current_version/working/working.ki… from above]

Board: 2 copper layers, 114.3 x 40.6 mm, 13 parts (0 on the bottom side), 11 nets.

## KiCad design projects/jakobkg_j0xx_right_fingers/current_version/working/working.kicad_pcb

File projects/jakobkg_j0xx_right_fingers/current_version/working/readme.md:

# j0xx
 
## summary 
* id: jakobkg_j0xx_right_fingers
* user: jakobkg
* name: j0xx
* board: right_fingers
* repo: https://github.com/jakobkg/j0xx
* src_file_repo_kicad_pcb: pcb/right_fingers/right_fingers.kicad_pcb
* src_file_repo_kicad_pcb_link: https://github.com/jakobkg/j0xx/tree/main/pcb/right_fingers/right_fingers.kicad_pcb
* src_file_repo_kicad_sch: pcb/right_fingers/right_fingers.kicad_sch
* src_file_repo_kicad_sch_link: https://github.com/jakobkg/j0xx/tree/main/pcb/right_fingers/right_fingers.kicad_sch

* src_file_repo_sch: 
* src_file_repo_sch_link: https://github.com/jakobkg/j0xx/tree/main/
* full details link: https://github.com/oomlout/oomlout_oomp_project_bot_v_2/tree/main/projects/jakobkg_j0xx_right_fingers/current_version/working

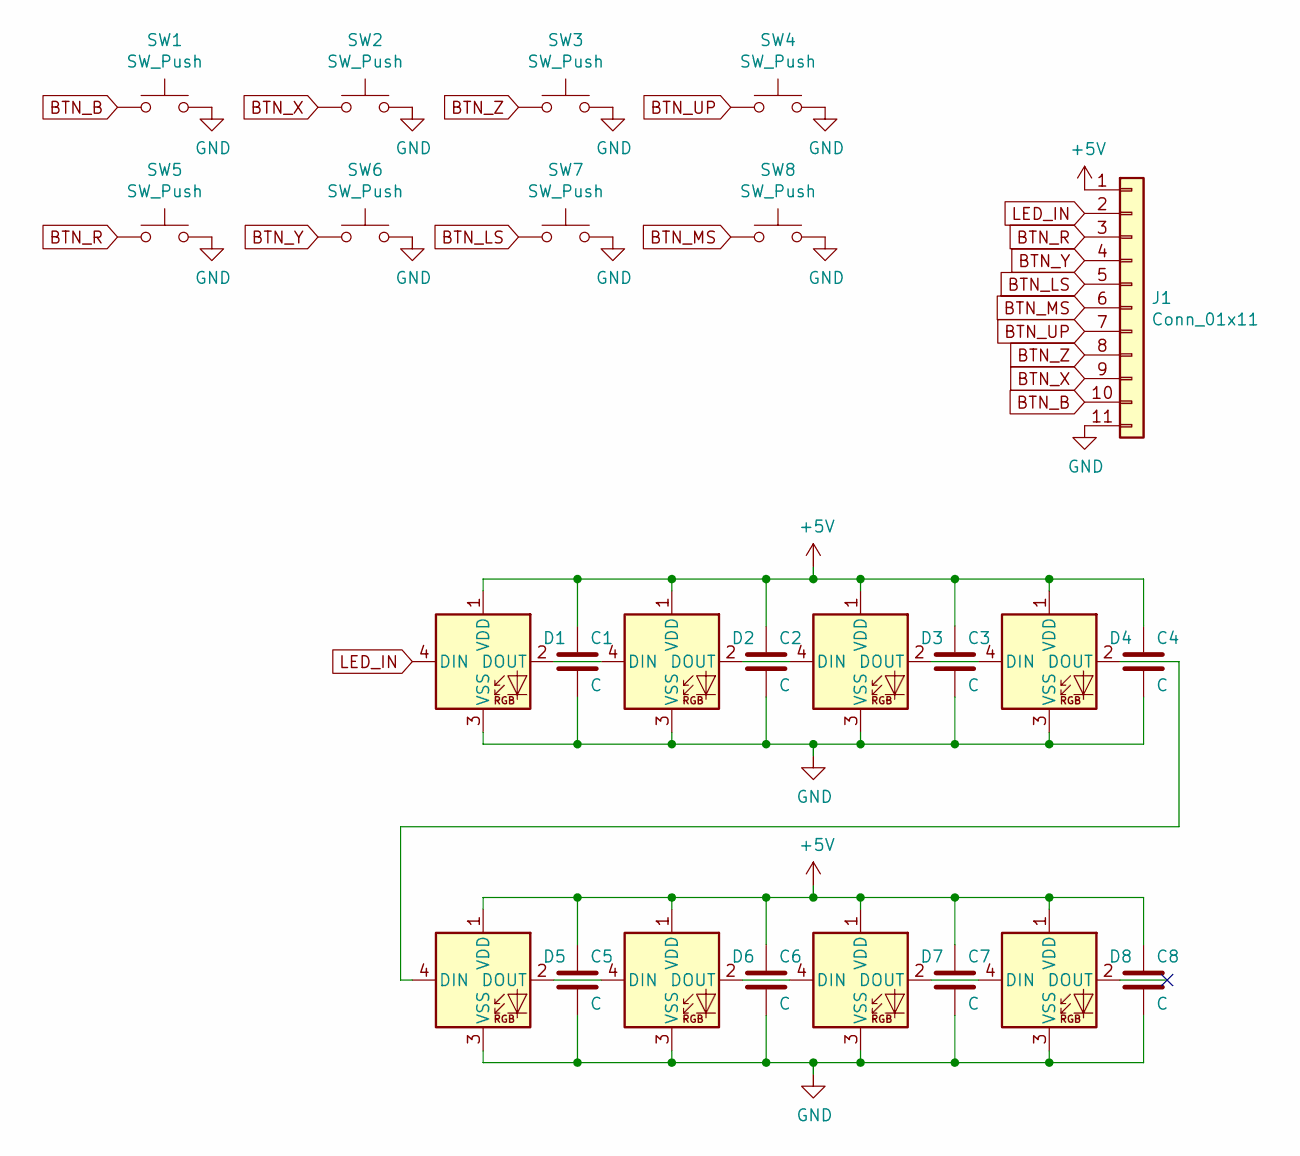
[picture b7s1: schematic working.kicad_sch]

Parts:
C1, C2, C3, C4, C5, C6, C7, C8: C; C_0805_2012Metric
D1, D2, D3, D4, D5, D6, D7, D8: WS2812B; LED_WS2812B_PLCC4_5.0x5.0mm_P3.2mm
J1: Conn_01x11; PinHeader_1x11_P2.54mm_Vertical
SW1, SW2, SW3, SW4, SW5, SW6, SW7, SW8: SW_Push; MX+Choc_socket

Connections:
+5V: C1.1, C2.1, C3.1, C4.1, C5.1, C6.1, C7.1, C8.1, D1.1 (VDD), D2.1 (VDD), D3.1 (VDD), D4.1 (VDD), D5.1 (VDD), D6.1 (VDD), D7.1 (VDD), D8.1 (VDD), J1.1
BTN_B: J1.10, SW1.1
BTN_LS: J1.5, SW7.1
BTN_MS: J1.6, SW8.1
BTN_R: J1.3, SW5.1
BTN_UP: J1.7, SW4.1
BTN_X: J1.9, SW2.1
BTN_Y: J1.4, SW6.1
BTN_Z: J1.8, SW3.1
GND: C1.2, C2.2, C3.2, C4.2, C5.2, C6.2, C7.2, C8.2, D1.3 (VSS), D2.3 (VSS), D3.3 (VSS), D4.3 (VSS), D5.3 (VSS), D6.3 (VSS), D7.3 (VSS), D8.3 (VSS), J1.11, SW1.2, SW2.2, SW3.2, SW4.2, SW5.2, SW6.2, SW7.2, SW8.2
LED_IN: D1.4 (DIN), J1.2
unnamed: D1.2 (DOUT), D2.4 (DIN)
unnamed: D2.2 (DOUT), D3.4 (DIN)
unnamed: D3.2 (DOUT), D4.4 (DIN)
unnamed: D4.2 (DOUT), D5.4 (DIN)
unnamed: D5.2 (DOUT), D6.4 (DIN)
unnamed: D6.2 (DOUT), D7.4 (DIN)
unnamed: D7.2 (DOUT), D8.4 (DIN)
